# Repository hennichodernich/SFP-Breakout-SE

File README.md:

# Modified SFP-Breakout-Board

This is a modified version of Anders Wallins SFP Breakout Board https://github.com/aewallin/SFP-Breakout-Board

Like the original this works as a SFP fibre-optical transciever simple breakout board up to at least 1 Gbit/s.

What's changed is that is has
* single-ended TX and RX outputs/inputs with SMA connectors (similar to Anders' SFP2SMA_2018.03 board, but with LVDS/LVPECL converters instead of baluns and op amps)
* different (cheaper) LDO

What's unchanged is
* connector and cage for SFP or SFP+ transciever
* +3V3 power for transciever
* Three status LEDs for TX_FAULT, LOS, and MOD_ABS
* jumpers for SFP rate-select settings.

Licensed under CERN OHL v. 1.2

See also these other similar projects:

* https://github.com/aewallin/SFP2SMA_2018.03  single-ended input/output, with op-amp and transformer coupling to SFP
* https://osmocom.org/projects/misc-hardware/wiki/Sfp-experimenter
* https://osmocom.org/projects/misc-hardware/wiki/Sfp-breakout
* Multi-SFP crate https://www.ohwr.org/project/sfp-plus-i2c/wikis/home

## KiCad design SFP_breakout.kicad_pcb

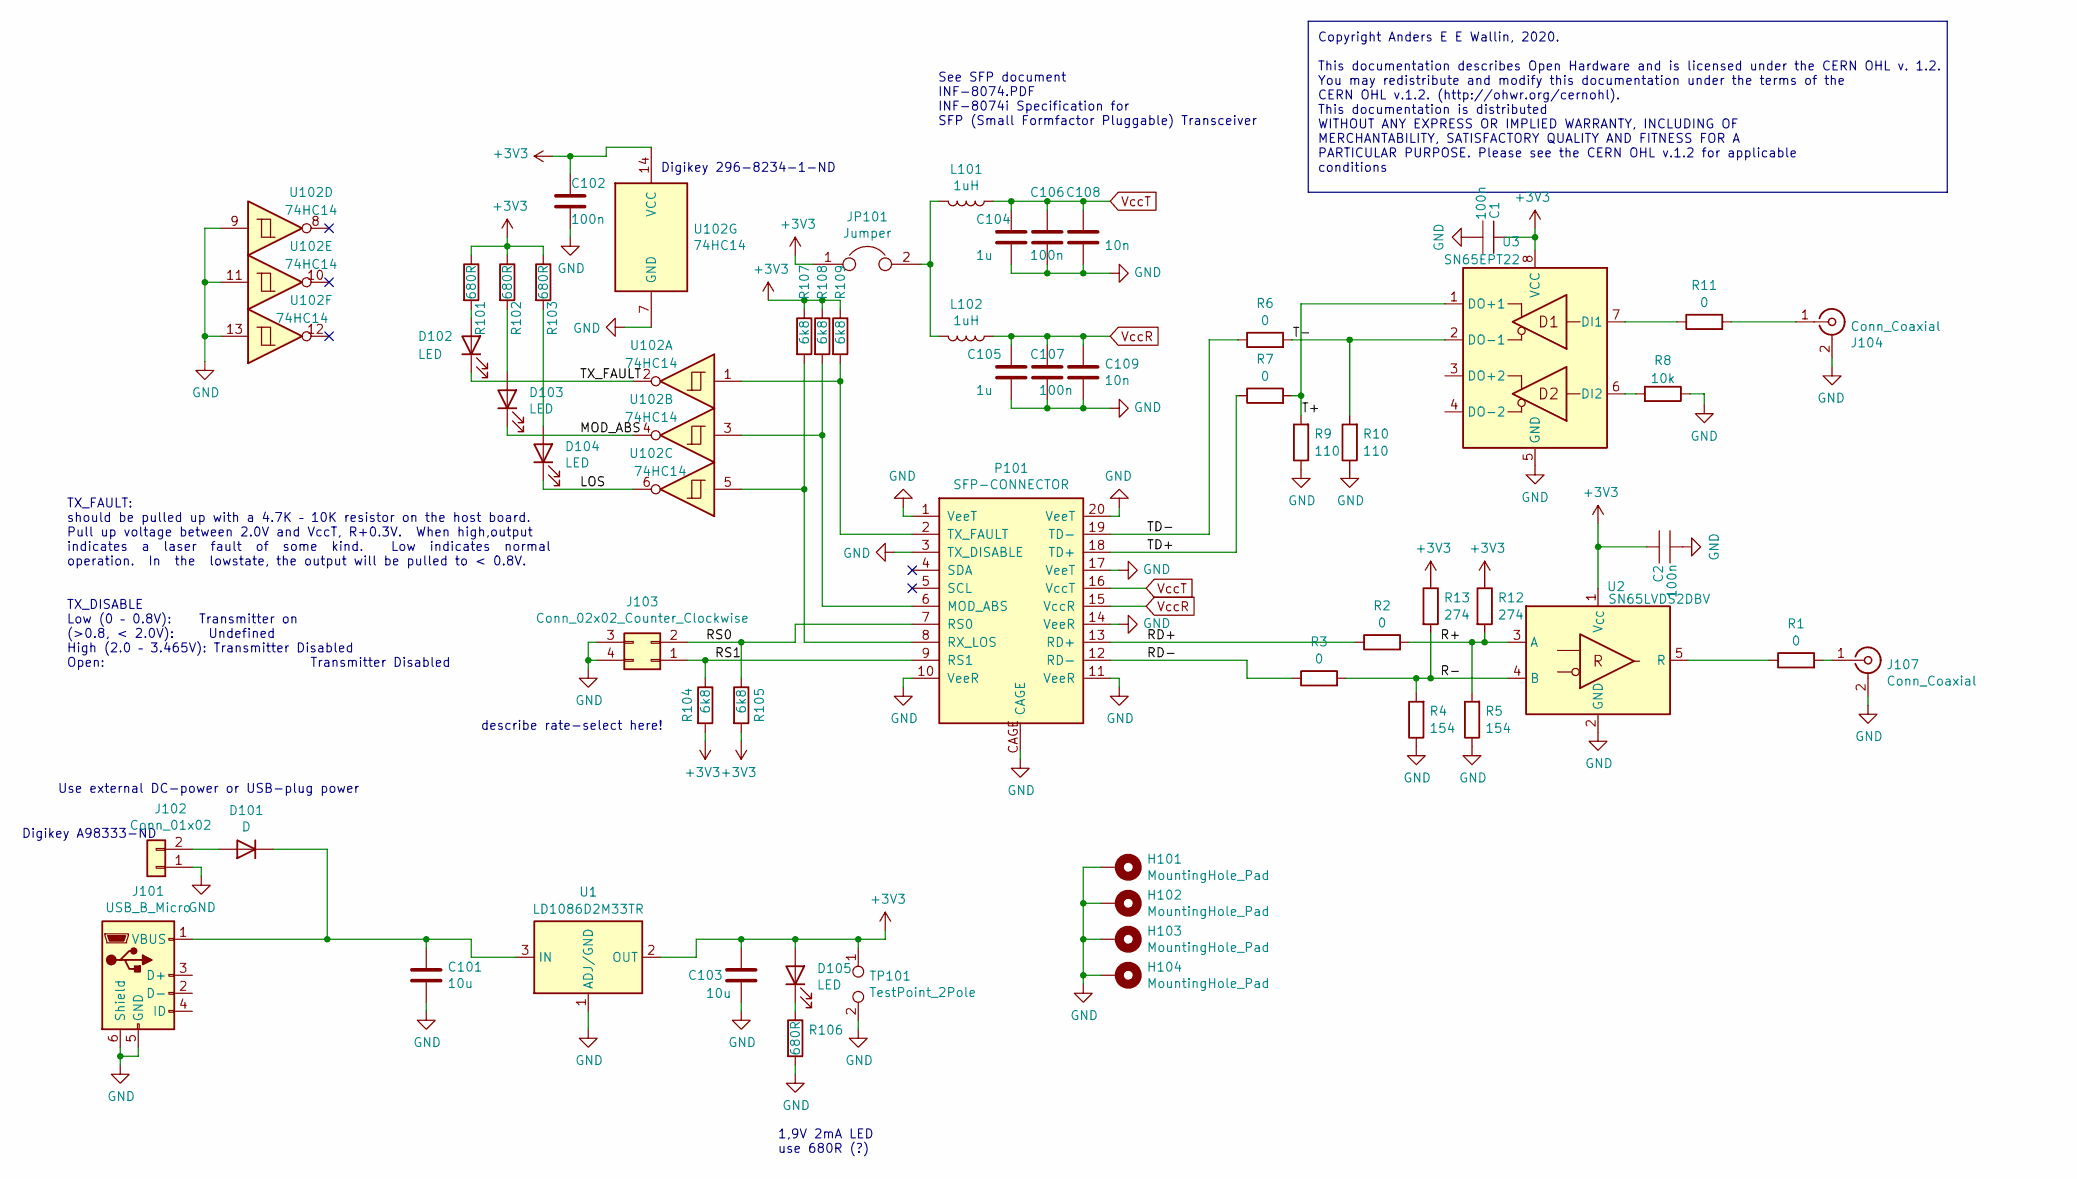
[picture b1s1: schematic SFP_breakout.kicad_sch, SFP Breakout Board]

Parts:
C1, C2: 100n; C_0402_1005Metric
C101, C103: 10u; C_0805_2012Metric
C102, C106, C107: 100n; C_0603_1608Metric
C104, C105: 1u; C_0603_1608Metric
C108, C109: 10n; C_0603_1608Metric
D101: D; DIODE_DO-214BA
D102, D103, D104, D105: LED; LED_0603_1608Metric
H101, H102, H103, H104: MountingHole_Pad; MountingHole_3.2mm_M3_DIN965_Pad
J101: USB_B_Micro; USB_Micro-B_Molex-105017-0001
J102: Conn_01x02; TerminalBlock_TE_282834-2_1x02_P2.54mm_Horizontal
J103: Conn_02x02_Counter_Clockwise; PinHeader_2x02_P2.54mm_Vertical
J104, J107: Conn_Coaxial; SMA_Samtec_SMA-J-P-X-ST-EM1_EdgeMount
JP101: Jumper; PinHeader_1x02_P2.54mm_Vertical
L101, L102: 1uH; L_0805_2012Metric
P101: SFP-CONNECTOR; Connector_SFP_and_Cage
R1, R2, R3, R6, R7, R11: 0; R_0402_1005Metric
R4, R5: 154; R_0402_1005Metric
R8: 10k; R_0402_1005Metric
R9, R10: 110; R_0402_1005Metric
R12, R13: 274; R_0402_1005Metric
R101, R102, R103, R106: 680R; R_0603_1608Metric
R104, R105, R107, R108, R109: 6k8; R_0603_1608Metric
TP101: TestPoint_2Pole; PinHeader_1x02_P2.54mm_Vertical
U1: LD1086D2M33TR; TO-263-3_TabPin2
U2: SN65LVDS2DBV; SOT-23-5
U3: SN65EPT22; VSSOP-8_3.0x3.0mm_P0.65mm
U102: 74HC14; TSSOP-14_4.4x5mm_P0.65mm

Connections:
+3V3: C1.1, C2.1, C102.1, C103.1, D105.2 (A), JP101.1, R12.1, R13.1, R101.1, R102.1, R103.1, R104.2, R105.2, R107.1, R108.1, R109.1, TP101.1, U1.2 (OUT), U2.1 (V_{CC}), U3.8 (VCC), U102.14 (VCC)
/LOS: D104.1 (K), U102.6
/MOD_ABS: D103.1 (K), U102.4
/R+: R2.2, R5.2, R12.2, U2.3 (A)
/R-: R3.2, R4.2, R13.2, U2.4 (B)
/RD+: P101.13 (RD+), R2.1
/RD-: P101.12 (RD-), R3.1
/RS0: J103.2, P101.7 (RS0), R105.1
/RS1: J103.1, P101.9 (RS1), R104.1
/T+: R7.2, R9.2, U3.1 (DO+1)
/T-: R6.2, R10.2, U3.2 (DO-1)
/TD+: P101.18 (TD+), R7.1
/TD-: P101.19 (TD-), R6.1
/TX_FAULT: D102.1 (K), U102.2
GND: C1.2, C2.2, C101.2, C102.2, C103.2, C104.2, C105.2, C106.2, C107.2, C108.2, C109.2, H101.1, H102.1, H103.1, H104.1, J101.5 (GND), J101.6 (Shield), J102.1, J103.3, J103.4, J104.2 (Ext), J107.2 (Ext), P101.1 (VeeT), P101.3 (TX_DISABLE), P101.10 (VeeR), P101.11 (VeeR), P101.14 (VeeR), P101.17 (VeeT), P101.20 (VeeT), P101.CAGE, R4.1, R5.1, R8.1, R9.1, R10.1, R106.2, TP101.2, U1.1 (ADJ/GND), U2.2 (GND), U3.5 (GND), U102.7 (GND), U102.9, U102.11, U102.13
unnamed: D101.2 (A), J102.2
unnamed: C101.1, D101.1 (K), J101.1 (VBUS), U1.3 (IN)
unnamed: D102.2 (A), R101.2
unnamed: D103.2 (A), R102.2
unnamed: D104.2 (A), R103.2
unnamed: D105.1 (K), R106.1
unnamed: J104.1 (In), R11.2
unnamed: J107.1 (In), R1.2
unnamed: JP101.2, L101.2, L102.2
unnamed: P101.6 (MOD_ABS), R108.2, U102.3
unnamed: P101.8 (RX_LOS), R107.2, U102.5
unnamed: P101.2 (TX_FAULT), R109.2, U102.1
unnamed: R1.1, U2.5 (R)
unnamed: R11.1, U3.7 (DI1)
unnamed: R8.2, U3.6 (DI2)
VccR: C105.1, C107.1, C109.1, L102.1, P101.15 (VccR)
VccT: C104.1, C106.1, C108.1, L101.1, P101.16 (VccT)

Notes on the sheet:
Digikey 296-8234-1-ND
1,9V 2mA LED use 680R (?)
Digikey A98333-ND
describe rate-select here!
Copyright Anders E E Wallin, 2020. This documentation describes Open Hardware and is licensed under the CERN OHL v. 1.2. You may redistribute and modify this documentation under the terms of the CERN OHL v.1.2. (http://ohwr.org/cernohl). This documentation is distributed WITHOUT ANY EXPRESS OR IMPL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
See SFP document INF-8074.PDF INF-8074i Specification for SFP (Small Formfactor Pluggable) Transceiver
TX_FAULT: should be pulled up with a 4.7K – 10K resistor on the host board. Pull up voltage between 2.0V and VccT, R+0.3V. When high,output indicates a laser fault of some kind. Low indicates normal operation. In the lowstate, the output will be pulled to < 0.8V. TX_DISABLE Low (0 – 0.8V): Transmit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
Use external DC-power or USB-plug power

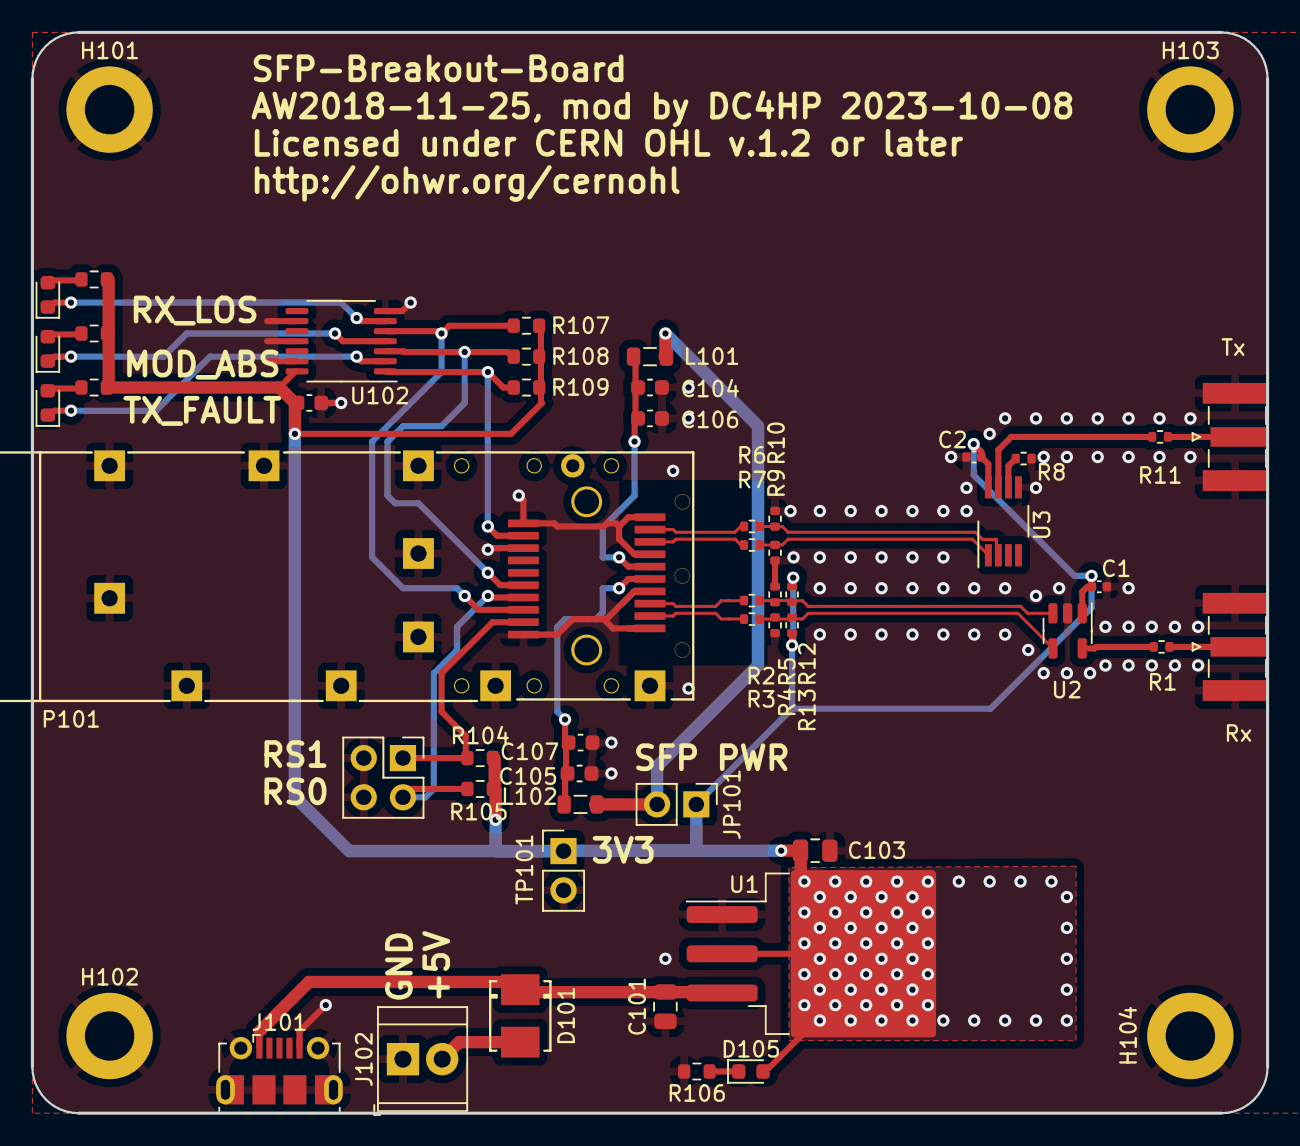
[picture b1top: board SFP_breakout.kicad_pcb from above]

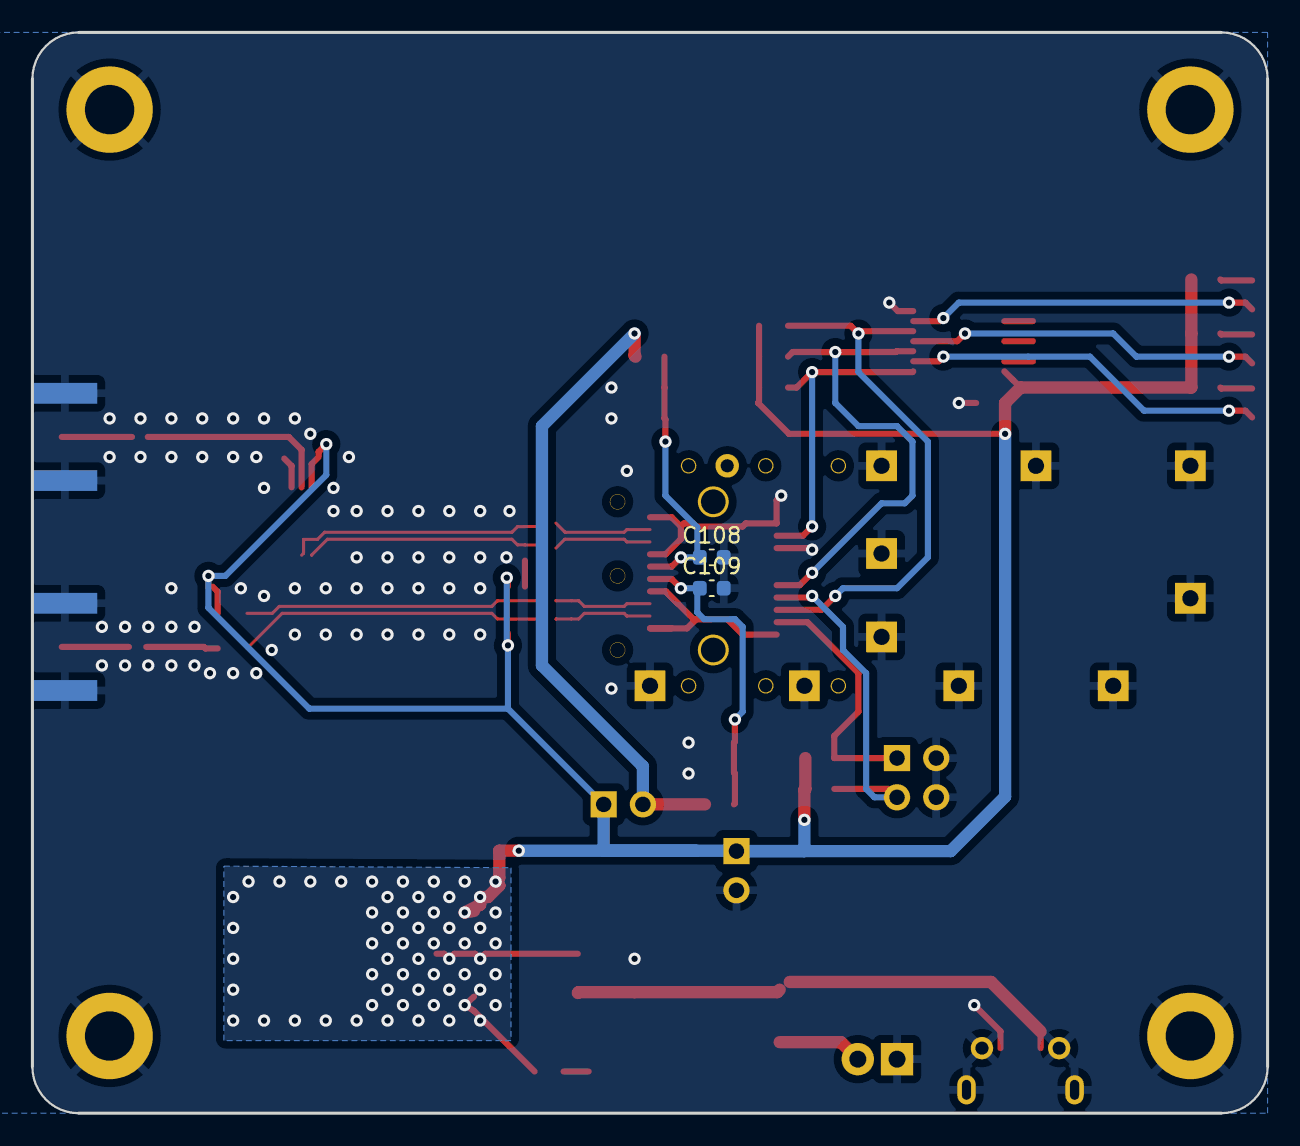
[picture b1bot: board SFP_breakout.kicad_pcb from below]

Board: 2 copper layers, 80.0 x 70.0 mm, 56 parts (2 on the bottom side), 32 nets.

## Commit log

2025-01-03 Added PDF version of schematic
2025-01-03 Added license in README

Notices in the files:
SFP_breakout.kicad_pcb:
Licensed under CERN OHL v.1.2 or later
